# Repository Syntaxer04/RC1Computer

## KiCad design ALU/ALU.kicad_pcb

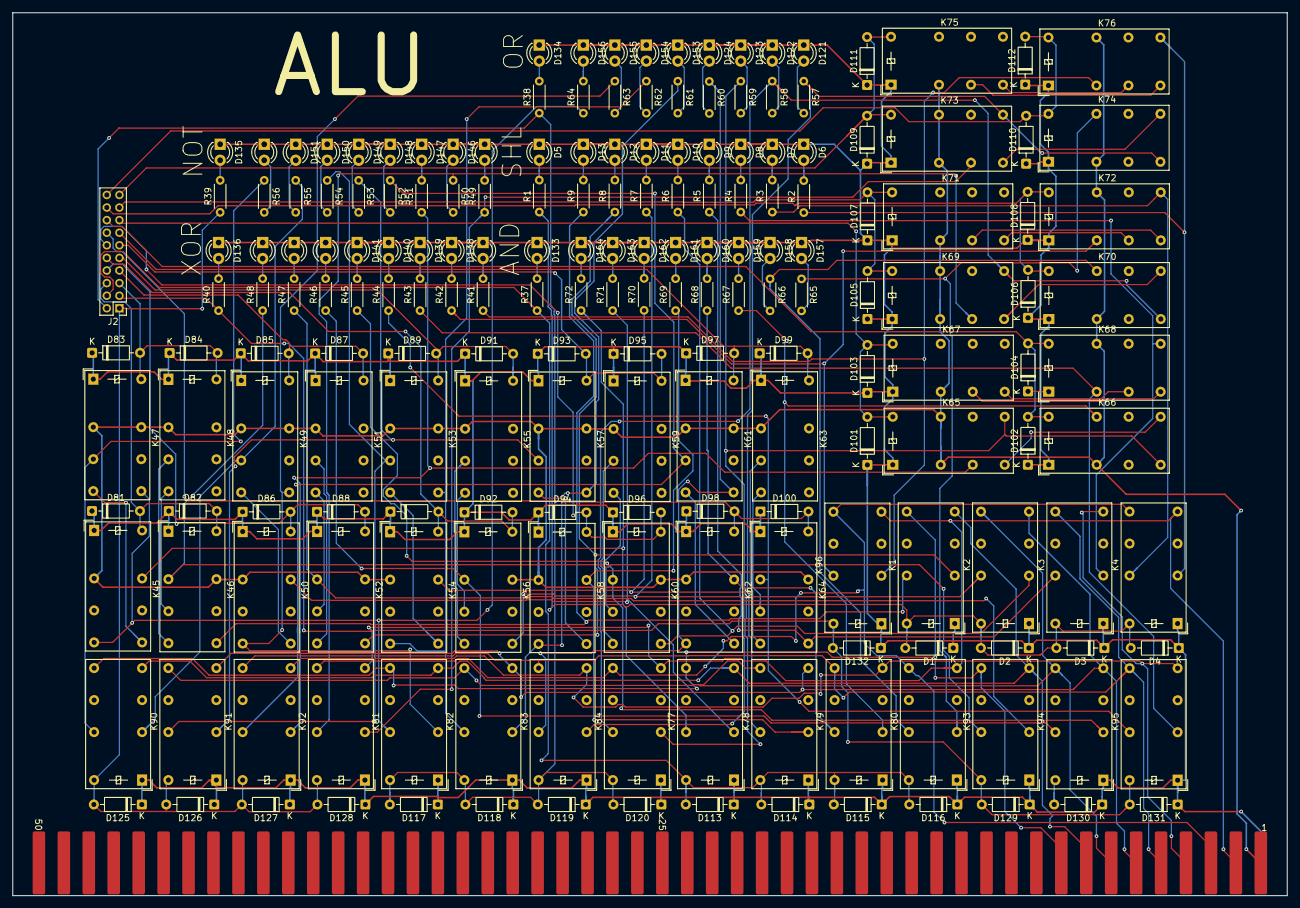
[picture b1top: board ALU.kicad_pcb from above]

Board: 2 copper layers, 202.4 x 140.2 mm, 196 parts (0 on the bottom side), 142 nets.

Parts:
D1, D2, D3, D4, D81, D82, D83, D84, D85, D86, D87, D88, D89, D90, D91, D92, D93, D94, D95, D96, D97, D98, D99, D100, D101, D102, D103, D104, D105, D106, D107, D108, D109, D110, D111, D112, D113, D114, D115, D116, D117, D118, D119, D120, D125, D126, D127, D128, D129, D130, D131, D132: 1N914; D_DO-35_SOD27_P7.62mm_Horizontal
D5, D6, D7, D8, D9, D10, D11, D12, D13, D121, D122, D123, D124, D133, D134, D135, D136, D137, D138, D139, D140, D141, D142, D143, D144, D145, D146, D147, D148, D149, D150, D151, D152, D153, D154, D155, D156, D157, D158, D159, D160, D161, D162, D163, D164: LED; LED_D3.0mm
J2: Conn_02x10_Odd_Even; PinHeader_2x10_P2.00mm_Vertical
K1, K2, K3, K4, K45, K46, K47, K48, K49, K50, K51, K52, K53, K54, K55, K56, K57, K58, K59, K60, K61, K62, K63, K64, K65, K66, K67, K68, K69, K70, K71, K72, K73, K74, K75, K76, K77, K78, K79, K80, K81, K82, K83, K84, K89, K90, K91, K92, K93, K94, K95, K96: HK19F-DCxxV-SHC; Relay_DPDT_Finder_30.22
R1, R2, R3, R4, R5, R6, R7, R8, R9, R37, R38, R39, R40, R41, R42, R43, R44, R45, R46, R47, R48, R49, R50, R51, R52, R53, R54, R55, R56, R57, R58, R59, R60, R61, R62, R63, R64, R65, R66, R67, R68, R69, R70, R71, R72: R; R_Axial_DIN0204_L3.6mm_D1.6mm_P5.08mm_Horizontal
U1: Conn_RC_Male_100

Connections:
unnamed: D1.2 (A), D2.2 (A), D3.2 (A), D4.2 (A), K1.A2, K2.A2, K3.A2, K4.A2, R1.1
unnamed: D1.1 (K), D2.1 (K), D3.1 (K), D4.1 (K), D5.1 (K), D6.1 (K), D7.1 (K), D8.1 (K), D9.1 (K), D10.1 (K), D11.1 (K), D12.1 (K), D13.1 (K), D81.1 (K), D82.1 (K), D83.1 (K), D84.1 (K), D85.1 (K), D86.1 (K), D87.1 (K), D88.1 (K), D89.1 (K), D90.1 (K), D91.1 (K), D92.1 (K), D93.1 (K), D94.1 (K), D95.1 (K), D96.1 (K), D97.1 (K), D98.1 (K), D99.1 (K), D100.1 (K), D101.1 (K), D102.1 (K), D103.1 (K), D105.1 (K), D106.1 (K), D107.1 (K), D108.1 (K), D109.1 (K), D110.1 (K), D111.1 (K), D112.1 (K), D113.1 (K), D114.1 (K), D115.1 (K), D116.1 (K), D117.1 (K), D118.1 (K), D119.1 (K), D120.1 (K), D121.1 (K), D122.1 (K), D123.1 (K), D124.1 (K), D125.1 (K), D126.1 (K), D127.1 (K), D128.1 (K), D129.1 (K), D130.1 (K), D131.1 (K), D132.1 (K), D133.1 (K), D134.1 (K), D135.1 (K), D136.1 (K), D137.1 (K), D138.1 (K), D139.1 (K), D140.1 (K), D141.1 (K), D142.1 (K), D143.1 (K), D144.1 (K), D145.1 (K), D146.1 (K), D147.1 (K), D148.1 (K), D149.1 (K), D150.1 (K), D151.1 (K), D152.1 (K), D153.1 (K), D154.1 (K), D155.1 (K), D156.1 (K), D157.1 (K), D158.1 (K), D159.1 (K), D160.1 (K), D161.1 (K), D162.1 (K), D163.1 (K), D164.1 (K), K1.A1, K2.A1, K3.A1, K4.A1, K45.A1, K46.A1, K47.A1, K48.A1, K49.A1, K50.A1, K51.A1, K52.A1, K53.A1, K54.A1, K55.A1, K56.A1, K57.A1, K58.A1, K59.A1, K60.A1, K61.A1, K62.A1, K63.A1, K64.A1, K65.A1, K66.A1, K67.A1, K69.A1, K70.A1, K71.A1, K72.A1, K73.A1, K74.A1, K75.A1, K76.A1, K77.A1, K78.A1, K79.A1, K80.A1, K81.A1, K82.A1, K83.A1, K84.A1, K89.A1, K90.A1, K91.A1, K92.A1, K93.A1, K94.A1, K95.A1, K96.A1, U1.51 (GND)
unnamed: D5.2 (A), R1.2
unnamed: D6.2 (A), R2.2
unnamed: D7.2 (A), R3.2
unnamed: D8.2 (A), R4.2
unnamed: D9.2 (A), R5.2
unnamed: D10.2 (A), R6.2
unnamed: D11.2 (A), R7.2
unnamed: D12.2 (A), R8.2
unnamed: D13.2 (A), R9.2
unnamed: D81.2 (A), D82.2 (A), J2.6, K45.A2, K46.A2
unnamed: D83.2 (A), D84.2 (A), J2.5, K47.A2, K48.A2
unnamed: D85.2 (A), D87.2 (A), J2.7, K49.A2, K51.A2
unnamed: D86.2 (A), D88.2 (A), J2.8, K50.A2, K52.A2
unnamed: D89.2 (A), D91.2 (A), J2.9, K53.A2, K55.A2
unnamed: D90.2 (A), D92.2 (A), J2.10, K54.A2, K56.A2
unnamed: D93.2 (A), D95.2 (A), J2.11, K57.A2, K59.A2
unnamed: D94.2 (A), D96.2 (A), J2.12, K58.A2, K60.A2
unnamed: D97.2 (A), D99.2 (A), J2.13, K61.A2, K63.A2
unnamed: D98.2 (A), D100.2 (A), J2.14, K62.A2, K64.A2
unnamed: D101.2 (A), D103.2 (A), J2.15, K65.A2, K67.A2
unnamed: D102.2 (A), D104.2 (A), J2.16, K66.A2, K68.A2
unnamed: D104.1 (K), K68.A1
unnamed: D105.2 (A), D107.2 (A), J2.17, K69.A2, K71.A2
unnamed: D106.2 (A), D108.2 (A), J2.18, K70.A2, K72.A2
unnamed: D109.2 (A), D111.2 (A), J2.19, K73.A2, K75.A2
unnamed: D110.2 (A), D112.2 (A), J2.20, K74.A2, K76.A2
unnamed: D113.2 (A), D114.2 (A), D115.2 (A), D116.2 (A), J2.4, K77.A2, K78.A2, K79.A2, K80.A2, R37.1
unnamed: D117.2 (A), D118.2 (A), D119.2 (A), D120.2 (A), J2.2, K81.A2, K82.A2, K83.A2, K84.A2, R38.1
unnamed: D121.2 (A), R57.2
unnamed: D122.2 (A), R58.2
unnamed: D123.2 (A), R59.2
unnamed: D124.2 (A), R60.2
unnamed: D125.2 (A), D126.2 (A), D127.2 (A), D128.2 (A), J2.1, K89.A2, K90.A2, K91.A2, K92.A2, R39.1
unnamed: D129.2 (A), D131.2 (A), D132.2 (A), J2.3, K93.A2, K95.A2, K96.A2, R40.1
unnamed: D130.2 (A), K94.A2
unnamed: D133.2 (A), R37.2
unnamed: D134.2 (A), R38.2
unnamed: D135.2 (A), R39.2
unnamed: D136.2 (A), R40.2
unnamed: D137.2 (A), R41.2
unnamed: D138.2 (A), R42.2
unnamed: D139.2 (A), R43.2
unnamed: D140.2 (A), R44.2
unnamed: D141.2 (A), R45.2
unnamed: D142.2 (A), R46.2
unnamed: D143.2 (A), R47.2
unnamed: D144.2 (A), R48.2
unnamed: D145.2 (A), R49.2
unnamed: D146.2 (A), R50.2
unnamed: D147.2 (A), R51.2
unnamed: D148.2 (A), R52.2
unnamed: D149.2 (A), R53.2
unnamed: D150.2 (A), R54.2
unnamed: D151.2 (A), R55.2
unnamed: D152.2 (A), R56.2
unnamed: D153.2 (A), R61.2
unnamed: D154.2 (A), R62.2
unnamed: D155.2 (A), R63.2
unnamed: D156.2 (A), R64.2
unnamed: D157.2 (A), R65.2
unnamed: D158.2 (A), R66.2
unnamed: D159.2 (A), R67.2
unnamed: D160.2 (A), R68.2
unnamed: D161.2 (A), R69.2
unnamed: D162.2 (A), R70.2
unnamed: D163.2 (A), R71.2
unnamed: D164.2 (A), R72.2
unnamed: K1.11, K52.24, R8.1
unnamed: K1.21, K46.24, R9.1
unnamed: K2.11, K60.24, R6.1
unnamed: K2.21, K56.24, R7.1
unnamed: K3.11, K68.24, R4.1
unnamed: K3.21, K64.24, R5.1
unnamed: K4.11, K76.24, R2.1
unnamed: K4.21, K72.24, R3.1
unnamed: K45.14, K47.24, K81.21, R64.1
unnamed: K45.21, K77.21, R72.1
unnamed: K45.24, K47.14
unnamed: K46.11, K93.21, R48.1
unnamed: K46.12, K48.14
unnamed: K46.14, K48.12
unnamed: K47.12, K89.21, R56.1
unnamed: K49.12, K89.11, R55.1
unnamed: K49.14, K50.24
unnamed: K49.24, K50.14, K81.11, R63.1
unnamed: K50.21, K77.11, R71.1
unnamed: K51.12, K52.14
unnamed: K51.14, K52.12
unnamed: K52.11, K93.11, R47.1
unnamed: K53.12, K90.21, R54.1
unnamed: K53.14, K54.24
unnamed: K53.24, K54.14, K82.21, R62.1
unnamed: K54.21, K78.21, R70.1
unnamed: K55.12, K56.14
unnamed: K55.14, K56.12
unnamed: K56.11, K94.21, R46.1
unnamed: K57.12, K90.11, R53.1
unnamed: K57.14, K58.24
unnamed: K57.24, K58.14, K82.11, R61.1
unnamed: K58.21, K78.11, R69.1
unnamed: K59.12, K60.14
unnamed: K59.14, K60.12
unnamed: K60.11, K94.11, R45.1
unnamed: K61.12, K91.21, R52.1
unnamed: K61.14, K62.24
unnamed: K61.24, K62.14, K83.21, R60.1
unnamed: K62.21, K79.21, R68.1
unnamed: K63.12, K64.14
unnamed: K63.14, K64.12
unnamed: K64.11, K95.21, R44.1
unnamed: K65.12, K91.11, R51.1
unnamed: K65.14, K66.24
unnamed: K65.24, K66.14, K83.11, R59.1
unnamed: K66.21, K79.11, R67.1
unnamed: K67.12, K68.14
unnamed: K67.14, K68.12
unnamed: K68.11, K95.11, R43.1
unnamed: K69.12, K92.21, R50.1
unnamed: K69.14, K70.24
unnamed: K69.24, K70.14, K84.21, R58.1
unnamed: K70.21, K80.21, R66.1
unnamed: K71.12, K72.14
unnamed: K71.14, K72.12
unnamed: K72.11, K96.21, R42.1
unnamed: K73.12, K92.11, R49.1
unnamed: K73.14, K74.24
unnamed: K73.24, K74.14, K84.11, R57.1
unnamed: K74.21, K80.11, R65.1
unnamed: K75.12, K76.14
unnamed: K75.14, K76.12
unnamed: K76.11, K96.11, R41.1
unnamed: K45.11, K46.21, K47.11, K47.21, K48.11, K49.11, K49.21, K50.11, K51.11, K52.21, K53.11, K53.21, K54.11, K55.11, K56.21, K57.11, K57.21, K58.11, K59.11, K60.21, K61.11, K61.21, K62.11, K63.11, K64.21, K65.11, K65.21, K66.11, K67.11, K68.21, K69.11, K69.21, K70.11, K71.11, K72.21, K73.11, K73.21, K74.11, K75.11, K76.21, U1.1 (5_Volt)
unnamed: K4.14, K80.14, K84.14, K92.14, K96.14, U1.2 (D0)
unnamed: K4.24, K80.24, K84.24, K92.24, K96.24, U1.3 (D1)
unnamed: K3.14, K79.14, K83.14, K91.14, K95.14, U1.4 (D2)
unnamed: K3.24, K79.24, K83.24, K91.24, K95.24, U1.5 (D3)
unnamed: K2.14, K78.14, K82.14, K90.14, K94.14, U1.6 (D4)
unnamed: K2.24, K78.24, K82.24, K90.24, K94.24, U1.7 (D5)
unnamed: K1.14, K77.14, K81.14, K89.14, K93.14, U1.8 (D6)
unnamed: K1.24, K77.24, K81.24, K89.24, K93.24, U1.9 (D7)

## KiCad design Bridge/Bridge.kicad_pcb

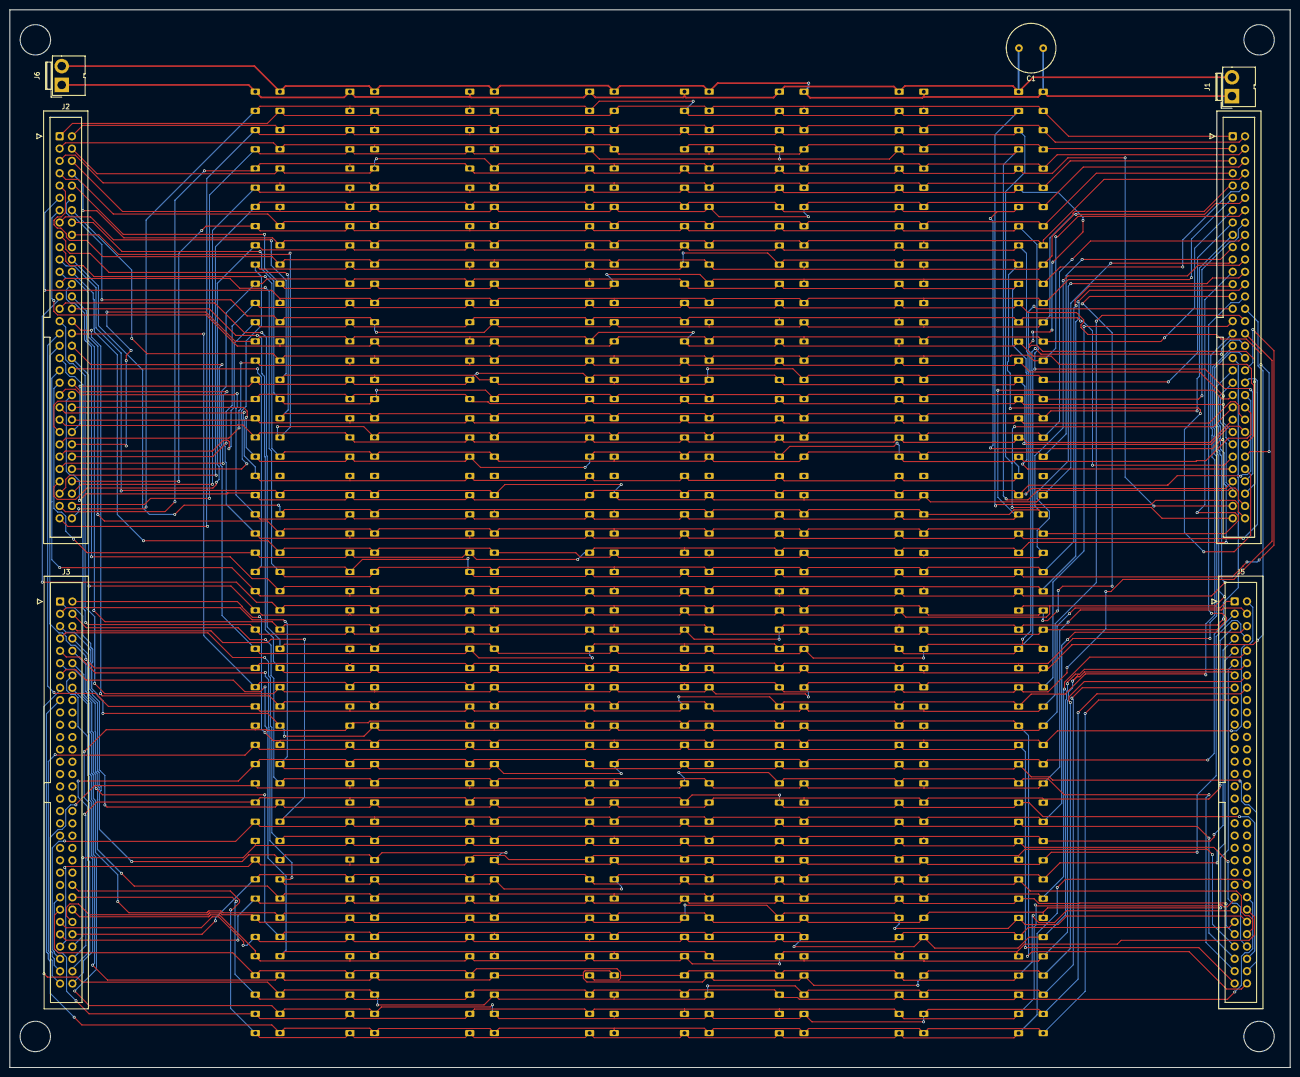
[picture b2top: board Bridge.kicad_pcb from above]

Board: 2 copper layers, 263.9 x 218.0 mm, 15 parts (0 on the bottom side), 99 nets.

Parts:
C1: C; C_Radial_D10.0mm_H12.5mm_P5.00mm
J1, J6: Conn_01x02_Socket; JWT_A3963_1x02_P3.96mm_Vertical
J2, J3, J4, J5: Conn_02x32_Counter_Clockwise; IDC-Header_2x32_P2.54mm_Vertical
U1, U2, U3, U4, U5, U6, U7, U8: Conn_RC_Female_100

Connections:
A0: J3.5, J5.5, U1.38 (A0), U2.38 (A0), U3.38 (A0), U4.38 (A0), U5.38 (A0), U6.38 (A0), U7.38 (A0), U8.38 (A0)
A1: J3.6, J5.6, U1.39 (A1), U2.39 (A1), U3.39 (A1), U4.39 (A1), U5.39 (A1), U6.39 (A1), U7.39 (A1), U8.39 (A1)
A2: J3.7, J5.7, U1.40 (A2), U2.40 (A2), U3.40 (A2), U4.40 (A2), U5.40 (A2), U6.40 (A2), U7.40 (A2), U8.40 (A2)
A3: J3.8, J5.8, U1.41 (A3), U2.41 (A3), U3.41 (A3), U4.41 (A3), U5.41 (A3), U6.41 (A3), U7.41 (A3), U8.41 (A3)
A4: J3.9, J5.9, U1.42 (A4), U2.42 (A4), U3.42 (A4), U4.42 (A4), U5.42 (A4), U6.42 (A4), U7.42 (A4), U8.42 (A4)
A5: J3.10, J5.10, U1.43 (A5), U2.43 (A5), U3.43 (A5), U4.43 (A5), U5.43 (A5), U6.43 (A5), U7.43 (A5), U8.43 (A5)
A6: J3.11, J5.11, U1.44 (A6), U2.44 (A6), U3.44 (A6), U4.44 (A6), U5.44 (A6), U6.44 (A6), U7.44 (A6), U8.44 (A6)
A7: J3.12, J5.12, U1.45 (A7), U2.45 (A7), U3.45 (A7), U4.45 (A7), U5.45 (A7), U6.45 (A7), U7.45 (A7), U8.45 (A7)
A8: J3.13, J5.13, U1.46 (A8), U2.46 (A8), U3.46 (A8), U4.46 (A8), U5.46 (A8), U6.46 (A8), U7.46 (A8), U8.46 (A8)
A9: J3.14, J5.14, U1.47 (A9), U2.47 (A9), U3.47 (A9), U4.47 (A9), U5.47 (A9), U6.47 (A9), U7.47 (A9), U8.47 (A9)
A10: J3.15, J5.15, U1.48 (A10), U2.48 (A10), U3.48 (A10), U4.48 (A10), U5.48 (A10), U6.48 (A10), U7.48 (A10), U8.48 (A10)
A11: J3.16, J5.16, U1.49 (A11), U2.49 (A11), U3.49 (A11), U4.49 (A11), U5.49 (A11), U6.49 (A11), U7.49 (A11), U8.49 (A11)
A12: J3.17, J5.17, U1.50 (A12), U2.50 (A12), U3.50 (A12), U4.50 (A12), U5.50 (A12), U6.50 (A12), U7.50 (A12), U8.50 (A12)
A13: J2.64, J4.64, U1.52 (A13), U2.52 (A13), U3.52 (A13), U4.52 (A13), U5.52 (A13), U6.52 (A13), U7.52 (A13), U8.52 (A13)
A14: J2.63, J4.63, U1.53 (A14), U2.53 (A14), U3.53 (A14), U4.53 (A14), U5.53 (A14), U6.53 (A14), U7.53 (A14), U8.53 (A14)
A15: J2.62, J4.62, U1.54 (A15), U2.54 (A15), U3.54 (A15), U4.54 (A15), U5.54 (A15), U6.54 (A15), U7.54 (A15), U8.54 (A15)
ALD: J2.18, J4.18, U1.19 (ALD), U2.19 (ALD), U3.19 (ALD), U4.19 (ALD), U5.19 (ALD), U6.19 (ALD), U7.19 (ALD), U8.19 (ALD)
ASL: J2.22, J4.22, U1.23 (ASL), U2.23 (ASL), U3.23 (ASL), U4.23 (ASL), U5.23 (ASL), U6.23 (ASL), U7.23 (ASL), U8.23 (ASL)
BLD: J2.42, J4.42, U1.74 (BLD), U2.74 (BLD), U3.74 (BLD), U4.74 (BLD), U5.74 (BLD), U6.74 (BLD), U7.74 (BLD), U8.74 (BLD)
BSL: J2.44, J4.44, U1.72 (BSL), U2.72 (BSL), U3.72 (BSL), U4.72 (BSL), U5.72 (BSL), U6.72 (BSL), U7.72 (BSL), U8.72 (BSL)
CCRegLD: J2.35, J4.35, U1.81 (CCRegLD), U2.81 (CCRegLD), U3.81 (CCRegLD), U4.81 (CCRegLD), U5.81 (CCRegLD), U6.81 (CCRegLD), U7.81 (CCRegLD), U8.81 (CCRegLD)
CCRegSL: J2.34, J4.34, U1.82 (CCRegSL), U2.82 (CCRegSL), U3.82 (CCRegSL), U4.82 (CCRegSL), U5.82 (CCRegSL), U6.82 (CCRegSL), U7.82 (CCRegSL), U8.82 (CCRegSL)
CLD: J2.41, J4.41, U1.75 (CLD), U2.75 (CLD), U3.75 (CLD), U4.75 (CLD), U5.75 (CLD), U6.75 (CLD), U7.75 (CLD), U8.75 (CLD)
CSL: J2.43, J4.43, U1.73 (CSL), U2.73 (CSL), U3.73 (CSL), U4.73 (CSL), U5.73 (CSL), U6.73 (CSL), U7.73 (CSL), U8.73 (CSL)
Carry: J3.2, J5.2, U1.35 (Carry), U2.35 (Carry), U3.35 (Carry), U4.35 (Carry), U5.35 (Carry), U6.35 (Carry), U7.35 (Carry), U8.35 (Carry)
D0: J2.1, J4.1, U1.2 (D0), U2.2 (D0), U3.2 (D0), U4.2 (D0), U5.2 (D0), U6.2 (D0), U7.2 (D0), U8.2 (D0)
D1: J2.2, J4.2, U1.3 (D1), U2.3 (D1), U3.3 (D1), U4.3 (D1), U5.3 (D1), U6.3 (D1), U7.3 (D1), U8.3 (D1)
D2: J2.3, J4.3, U1.4 (D2), U2.4 (D2), U3.4 (D2), U4.4 (D2), U5.4 (D2), U6.4 (D2), U7.4 (D2), U8.4 (D2)
D3: J2.4, J4.4, U1.5 (D3), U2.5 (D3), U3.5 (D3), U4.5 (D3), U5.5 (D3), U6.5 (D3), U7.5 (D3), U8.5 (D3)
D4: J2.5, J4.5, U1.6 (D4), U2.6 (D4), U3.6 (D4), U4.6 (D4), U5.6 (D4), U6.6 (D4), U7.6 (D4), U8.6 (D4)
D5: J2.6, J4.6, U1.7 (D5), U2.7 (D5), U3.7 (D5), U4.7 (D5), U5.7 (D5), U6.7 (D5), U7.7 (D5), U8.7 (D5)
D6: J2.7, J4.7, U1.8 (D6), U2.8 (D6), U3.8 (D6), U4.8 (D6), U5.8 (D6), U6.8 (D6), U7.8 (D6), U8.8 (D6)
D7: J2.8, J4.8, U1.9 (D7), U2.9 (D7), U3.9 (D7), U4.9 (D7), U5.9 (D7), U6.9 (D7), U7.9 (D7), U8.9 (D7)
DLD: J2.19, J4.19, U1.20 (DLD), U2.20 (DLD), U3.20 (DLD), U4.20 (DLD), U5.20 (DLD), U6.20 (DLD), U7.20 (DLD), U8.20 (DLD)
DSL: J2.23, J4.23, U1.24 (DSL), U2.24 (DSL), U3.24 (DSL), U4.24 (DSL), U5.24 (DSL), U6.24 (DSL), U7.24 (DSL), U8.24 (DSL)
F1: J2.31, J4.31, U1.32 (F1), U2.32 (F1), U3.32 (F1), U4.32 (F1), U5.32 (F1), U6.32 (F1), U7.32 (F1), U8.32 (F1)
F2: J2.32, J4.32, U1.33 (F2), U2.33 (F2), U3.33 (F2), U4.33 (F2), U5.33 (F2), U6.33 (F2), U7.33 (F2), U8.33 (F2)
F3: J3.1, J5.1, U1.34 (F3), U2.34 (F3), U3.34 (F3), U4.34 (F3), U5.34 (F3), U6.34 (F3), U7.34 (F3), U8.34 (F3)
FREEZE: J2.39, J4.39, U1.77 (FREEZE), U2.77 (FREEZE), U3.77 (FREEZE), U4.77 (FREEZE), U5.77 (FREEZE), U6.77 (FREEZE), U7.77 (FREEZE), U8.77 (FREEZE)
HALT: J3.63, J5.63, U1.85 (HALT), U2.85 (HALT), U3.85 (HALT), U4.85 (HALT), U5.85 (HALT), U6.85 (HALT), U7.85 (HALT), U8.85 (HALT)
I0: J2.47, J4.47, U1.69 (I0), U2.69 (I0), U3.69 (I0), U4.69 (I0), U5.69 (I0), U6.69 (I0), U7.69 (I0), U8.69 (I0)
I1: J2.48, J4.48, U1.68 (I1), U2.68 (I1), U3.68 (I1), U4.68 (I1), U5.68 (I1), U6.68 (I1), U7.68 (I1), U8.68 (I1)
I2: J2.49, J4.49, U1.67 (I2), U2.67 (I2), U3.67 (I2), U4.67 (I2), U5.67 (I2), U6.67 (I2), U7.67 (I2), U8.67 (I2)
I3: J2.50, J4.50, U1.66 (I3), U2.66 (I3), U3.66 (I3), U4.66 (I3), U5.66 (I3), U6.66 (I3), U7.66 (I3), U8.66 (I3)
I4: J2.51, J4.51, U1.65 (I4), U2.65 (I4), U3.65 (I4), U4.65 (I4), U5.65 (I4), U6.65 (I4), U7.65 (I4), U8.65 (I4)
I5: J2.52, J4.52, U1.64 (I5), U2.64 (I5), U3.64 (I5), U4.64 (I5), U5.64 (I5), U6.64 (I5), U7.64 (I5), U8.64 (I5)
I6: J2.53, J4.53, U1.63 (I6), U2.63 (I6), U3.63 (I6), U4.63 (I6), U5.63 (I6), U6.63 (I6), U7.63 (I6), U8.63 (I6)
I7: J2.54, J4.54, U1.62 (I7), U2.62 (I7), U3.62 (I7), U4.62 (I7), U5.62 (I7), U6.62 (I7), U7.62 (I7), U8.62 (I7)
IALU: J2.59, J4.59, U1.57 (IALU), U2.57 (IALU), U3.57 (IALU), U4.57 (IALU), U5.57 (IALU), U6.57 (IALU), U7.57 (IALU), U8.57 (IALU)
IGOTO: J2.60, J4.60, U1.56 (IGOTO), U2.56 (IGOTO), U3.56 (IGOTO), U4.56 (IGOTO), U5.56 (IGOTO), U6.56 (IGOTO), U7.56 (IGOTO), U8.56 (IGOTO)
IINC: J2.58, J4.58, U1.58 (IINC), U2.58 (IINC), U3.58 (IINC), U4.58 (IINC), U5.58 (IINC), U6.58 (IINC), U7.58 (IINC), U8.58 (IINC)
ILOD: J2.57, J4.57, U1.59 (ILOD), U2.59 (ILOD), U3.59 (ILOD), U4.59 (ILOD), U5.59 (ILOD), U6.59 (ILOD), U7.59 (ILOD), U8.59 (ILOD)
IM16: J2.55, J4.55, U1.61 (IM16), U2.61 (IM16), U3.61 (IM16), U4.61 (IM16), U5.61 (IM16), U6.61 (IM16), U7.61 (IM16), U8.61 (IM16)
ISET: J2.61, J4.61, U1.55 (ISET), U2.55 (ISET), U3.55 (ISET), U4.55 (ISET), U5.55 (ISET), U6.55 (ISET), U7.55 (ISET), U8.55 (ISET)
ISTR: J2.56, J4.56, U1.60 (ISTR), U2.60 (ISTR), U3.60 (ISTR), U4.60 (ISTR), U5.60 (ISTR), U6.60 (ISTR), U7.60 (ISTR), U8.60 (ISTR)
IncLD: J2.40, J4.40, U1.76 (INCLD), U2.76 (INCLD), U3.76 (INCLD), U4.76 (INCLD), U5.76 (INCLD), U6.76 (INCLD), U7.76 (INCLD), U8.76 (INCLD)
IncSL: J2.26, J4.26, U1.27 (IncSL), U2.27 (IncSL), U3.27 (IncSL), U4.27 (IncSL), U5.27 (IncSL), U6.27 (IncSL), U7.27 (IncSL), U8.27 (IncSL)
InstLD: J2.36, J4.36, U1.80 (INSTLD), U2.80 (INSTLD), U3.80 (INSTLD), U4.80 (INSTLD), U5.80 (INSTLD), U6.80 (INSTLD), U7.80 (INSTLD), U8.80 (INSTLD)
InstSL: J2.24, J4.24, U1.25 (InstSL), U2.25 (InstSL), U3.25 (InstSL), U4.25 (InstSL), U5.25 (InstSL), U6.25 (InstSL), U7.25 (InstSL), U8.25 (InstSL)
J1LD: J2.15, J4.15, U1.16 (J1LD), U2.16 (J1LD), U3.16 (J1LD), U4.16 (J1LD), U5.16 (J1LD), U6.16 (J1LD), U7.16 (J1LD), U8.16 (J1LD)
J2LD: J2.16, J4.16, U1.17 (J2LD), U2.17 (J2LD), U3.17 (J2LD), U4.17 (J2LD), U5.17 (J2LD), U6.17 (J2LD), U7.17 (J2LD), U8.17 (J2LD)
JSL: J2.17, J4.17, U1.18 (JSL), U2.18 (JSL), U3.18 (JSL), U4.18 (JSL), U5.18 (JSL), U6.18 (JSL), U7.18 (JSL), U8.18 (JSL)
MEMCS: J3.64, J5.64, U1.84 (MEMSL), U2.84 (MEMSL), U3.84 (MEMSL), U4.84 (MEMSL), U5.84 (MEMSL), U6.84 (MEMSL), U7.84 (MEMSL), U8.84 (MEMSL)
MEMWRITE: J2.33, J4.33, U1.83 (MEMWRITE), U2.83 (MEMWRITE), U3.83 (MEMWRITE), U4.83 (MEMWRITE), U5.83 (MEMWRITE), U6.83 (MEMWRITE), U7.83 (MEMWRITE), U8.83 (MEMWRITE)
MHiLD: J2.12, J4.12, U1.13 (MHiLD), U2.13 (MHiLD), U3.13 (MHiLD), U4.13 (MHiLD), U5.13 (MHiLD), U6.13 (MHiLD), U7.13 (MHiLD), U8.13 (MHiLD)
MHiLoLD: J2.14, J4.14, U1.15 (MHiLoLD), U2.15 (MHiLoLD), U3.15 (MHiLoLD), U4.15 (MHiLoLD), U5.15 (MHiLoLD), U6.15 (MHiLoLD), U7.15 (MHiLoLD), U8.15 (MHiLoLD)
MHiSL: J2.46, J4.46, U1.70 (MHiSL), U2.70 (MHiSL), U3.70 (MHiSL), U4.70 (MHiSL), U5.70 (MHiSL), U6.70 (MHiSL), U7.70 (MHiSL), U8.70 (MHiSL)
MLoLD: J2.13, J4.13, U1.14 (MLoLD), U2.14 (MLoLD), U3.14 (MLoLD), U4.14 (MLoLD), U5.14 (MLoLD), U6.14 (MLoLD), U7.14 (MLoLD), U8.14 (MLoLD)
MLoSL: J2.45, J4.45, U1.71 (MLoSL), U2.71 (MLoSL), U3.71 (MLoSL), U4.71 (MLoSL), U5.71 (MLoSL), U6.71 (MLoSL), U7.71 (MLoSL), U8.71 (MLoSL)
MemREAD: J2.37, J4.37, U1.79 (MEMREAD), U2.79 (MEMREAD), U3.79 (MEMREAD), U4.79 (MEMREAD), U5.79 (MEMREAD), U6.79 (MEMREAD), U7.79 (MEMREAD), U8.79 (MEMREAD)
MemSL: J2.21, J4.21, U1.22 (MemSL), U2.22 (MemSL), U3.22 (MemSL), U4.22 (MemSL), U5.22 (MemSL), U6.22 (MemSL), U7.22 (MemSL), U8.22 (MemSL)
N0: J3.62, J5.62, U1.86 (NC), U2.86 (NC), U3.86 (NC), U4.86 (NC), U5.86 (NC), U6.86 (NC), U7.86 (NC), U8.86 (NC)
N1: J3.61, J5.61, U1.87 (NC), U2.87 (NC), U3.87 (NC), U4.87 (NC), U5.87 (NC), U6.87 (NC), U7.87 (NC), U8.87 (NC)
N2: J3.60, J5.60, U1.88 (NC), U2.88 (NC), U3.88 (NC), U4.88 (NC), U5.88 (NC), U6.88 (NC), U7.88 (NC), U8.88 (NC)
N3: J3.59, J5.59, U1.89 (NC), U2.89 (NC), U3.89 (NC), U4.89 (NC), U5.89 (NC), U6.89 (NC), U7.89 (NC), U8.89 (NC)
N4: J3.58, J5.58, U1.90 (NC), U2.90 (NC), U3.90 (NC), U4.90 (NC), U5.90 (NC), U6.90 (NC), U7.90 (NC), U8.90 (NC)
N5: J3.57, J5.57, U1.91 (NC), U2.91 (NC), U3.91 (NC), U4.91 (NC), U5.91 (NC), U6.91 (NC), U7.91 (NC), U8.91 (NC)
N6: J3.56, J5.56, U1.92 (NC), U2.92 (NC), U3.92 (NC), U4.92 (NC), U5.92 (NC), U6.92 (NC), U7.92 (NC), U8.92 (NC)
N7: J3.55, J5.55, U1.93 (NC), U2.93 (NC), U3.93 (NC), U4.93 (NC), U5.93 (NC), U6.93 (NC), U7.93 (NC), U8.93 (NC)
N8: J3.54, J5.54, U1.94 (NC), U2.94 (NC), U3.94 (NC), U4.94 (NC), U5.94 (NC), U6.94 (NC), U7.94 (NC), U8.94 (NC)
N9: J3.53, J5.53, U1.95 (NC), U2.95 (NC), U3.95 (NC), U4.95 (NC), U5.95 (NC), U6.95 (NC), U7.95 (NC), U8.95 (NC)
N10: J3.52, J5.52, U1.96 (NC), U2.96 (NC), U3.96 (NC), U4.96 (NC), U5.96 (NC), U6.96 (NC), U7.96 (NC), U8.96 (NC)
N11: J3.51, J5.51, U1.97 (NC), U2.97 (NC), U3.97 (NC), U4.97 (NC), U5.97 (NC), U6.97 (NC), U7.97 (NC), U8.97 (NC)
N12: J3.50, J5.50, U1.98 (NC), U2.98 (NC), U3.98 (NC), U4.98 (NC), U5.98 (NC), U6.98 (NC), U7.98 (NC), U8.98 (NC)
N13: J3.49, J5.49, U1.99 (NC), U2.99 (NC), U3.99 (NC), U4.99 (NC), U5.99 (NC), U6.99 (NC), U7.99 (NC), U8.99 (NC)
N14: J3.48, J5.48, U1.100 (NC), U2.100 (NC), U3.100 (NC), U4.100 (NC), U5.100 (NC), U6.100 (NC), U7.100 (NC), U8.100 (NC)
unnamed: C1.1, J1.1, J6.2, U1.1 (5_Volt), U2.1 (5_Volt), U3.1 (5_Volt), U4.1 (5_Volt), U5.1 (5_Volt), U6.1 (5_Volt), U7.1 (5_Volt), U8.1 (5_Volt)
unnamed: C1.2, J1.2, J6.1, U1.51 (GND), U2.51 (GND), U3.51 (GND), U4.51 (GND), U5.51 (GND), U6.51 (GND), U7.51 (GND), U8.51 (GND)
PCLD: J2.30, J4.30, U1.31 (PCLD), U2.31 (PCLD), U3.31 (PCLD), U4.31 (PCLD), U5.31 (PCLD), U6.31 (PCLD), U7.31 (PCLD), U8.31 (PCLD)
PCSL: J2.25, J4.25, U1.26 (PCSL), U2.26 (PCSL), U3.26 (PCSL), U4.26 (PCSL), U5.26 (PCSL), U6.26 (PCSL), U7.26 (PCSL), U8.26 (PCSL)
SIGN: J3.4, J5.4, U1.37 (SIGN), U2.37 (SIGN), U3.37 (SIGN), U4.37 (SIGN), U5.37 (SIGN), U6.37 (SIGN), U7.37 (SIGN), U8.37 (SIGN)
STEP: J2.38, J4.38, U1.78 (STEP), U2.78 (STEP), U3.78 (STEP), U4.78 (STEP), U5.78 (STEP), U6.78 (STEP), U7.78 (STEP), U8.78 (STEP)
XLD: J2.9, J4.9, U1.10 (XLD), U2.10 (XLD), U3.10 (XLD), U4.10 (XLD), U5.10 (XLD), U6.10 (XLD), U7.10 (XLD), U8.10 (XLD)
XSL: J2.27, J4.27, U1.28 (XSL), U2.28 (XSL), U3.28 (XSL), U4.28 (XSL), U5.28 (XSL), U6.28 (XSL), U7.28 (XSL), U8.28 (XSL)
XYLD: J2.11, J4.11, U1.12 (XYLD), U2.12 (XYLD), U3.12 (XYLD), U4.12 (XYLD), U5.12 (XYLD), U6.12 (XYLD), U7.12 (XYLD), U8.12 (XYLD)
XYSL: J2.29, J4.29, U1.30 (XYSL), U2.30 (XYSL), U3.30 (XYSL), U4.30 (XYSL), U5.30 (XYSL), U6.30 (XYSL), U7.30 (XYSL), U8.30 (XYSL)
YLD: J2.10, J4.10, U1.11 (YLD), U2.11 (YLD), U3.11 (YLD), U4.11 (YLD), U5.11 (YLD), U6.11 (YLD), U7.11 (YLD), U8.11 (YLD)
YSL: J2.28, J4.28, U1.29 (YSL), U2.29 (YSL), U3.29 (YSL), U4.29 (YSL), U5.29 (YSL), U6.29 (YSL), U7.29 (YSL), U8.29 (YSL)
Zero: J3.3, J5.3, U1.36 (Zero), U2.36 (Zero), U3.36 (Zero), U4.36 (Zero), U5.36 (Zero), U6.36 (Zero), U7.36 (Zero), U8.36 (Zero)

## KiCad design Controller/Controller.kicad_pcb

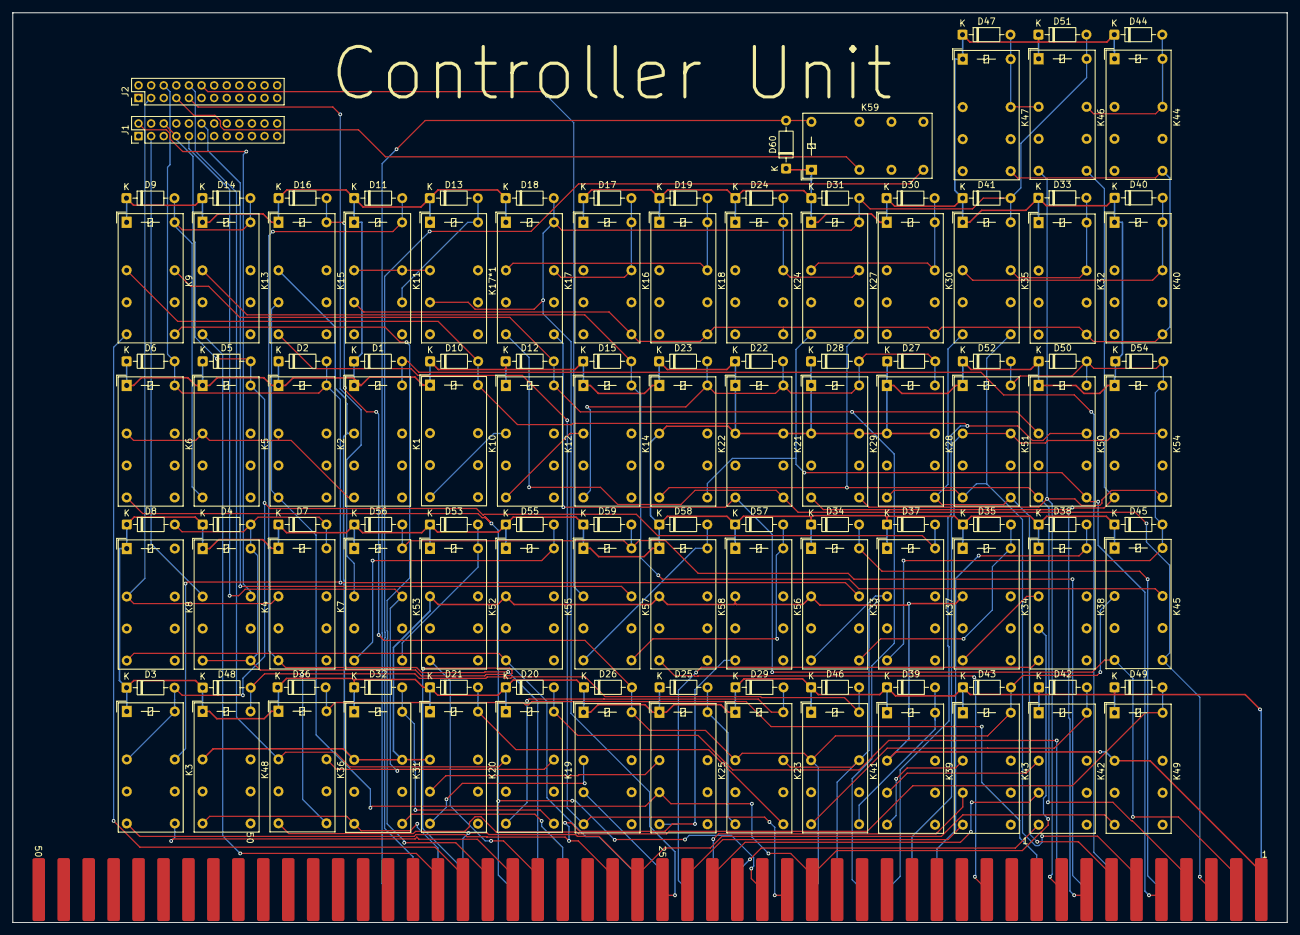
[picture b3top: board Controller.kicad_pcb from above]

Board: 2 copper layers, 202.3 x 144.4 mm, 123 parts (0 on the bottom side), 92 nets.

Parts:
D1, D2, D3, D4, D5, D6, D7, D8, D9, D10, D11, D12, D13, D14, D15, D16, D17, D18, D19, D20, D21, D22, D23, D24, D25, D26, D27, D28, D29, D30, D31, D32, D33, D34, D35, D36, D37, D38, D39, D40, D41, D42, D43, D44, D45, D46, D47, D48, D49, D50, D51, D52, D53, D54, D55, D56, D57, D58, D59, D60: 1N914; D_DO-35_SOD27_P7.62mm_Horizontal
J1, J2: Conn_02x12_Counter_Clockwise; PinHeader_2x12_P2.00mm_Vertical
K1, K2, K3, K4, K5, K6, K7, K8, K9, K10, K11, K12, K13, K14, K15, K16, K17, K17*1, K18, K19, K20, K21, K22, K23, K24, K25, K26, K27, K28, K29, K30, K31, K32, K33, K34, K35, K36, K37, K38, K39, K40, K41, K42, K43, K44, K45, K46, K47, K48, K49, K50, K51, K52, K53, K54, K55, K56, K57, K58, K59: HK19F-DCxxV-SHC; Relay_DPDT_Finder_30.22
U1: Conn_RC_Male_100

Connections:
5 V: K11.11, K11.21, K17*1.11
+5V: K1.11, K15.11, K20.11, K31.11, K31.21, K33.11, K34.11, K39.11, K48.11, K49.11, K52.11, K55.11, K56.11, K58.11, U1.1 (5_Volt)
ALD: K2.14, K15.12, K25.12, K38.12, U1.19 (ALD)
ALU: D1.2 (A), K1.A2, U1.57 (IALU)
ASL: K42.12, U1.23 (ASL)
BLD: K25.14, K38.14, U1.74 (BLD)
BSL: K42.14, U1.72 (BSL)
CLD: K26.12, U1.75 (CLD)
CSL: K43.12, U1.73 (CSL)
D0: K17.24, K21.14, K45.14, U1.2 (D0)
D1: K17.14, K21.24, K45.24, U1.3 (D1)
D2: K22.14, K27.24, K50.14, U1.4 (D2)
D3: K22.24, K27.14, K50.24, U1.5 (D3)
D4: K28.14, K35.24, K51.14, U1.6 (D4)
D5: K28.24, K35.14, K51.24, U1.7 (D5)
D6: K29.14, K46.24, K54.14, U1.8 (D6)
D7: K29.24, K46.14, K54.24, U1.9 (D7)
DLD: K15.14, K26.14, U1.20 (DLD)
DSL: K43.14, U1.24 (DSL)
F1: K9.24, U1.32 (F1)
F2: K9.14, U1.33 (F2)
F3: K13.14, U1.34 (F3)
GND: D1.1 (K), D2.1 (K), D3.1 (K), D4.1 (K), D5.1 (K), D6.1 (K), D7.1 (K), D8.1 (K), D9.1 (K), D10.1 (K), D11.1 (K), D12.1 (K), D13.1 (K), D14.1 (K), D15.1 (K), D16.1 (K), D17.1 (K), D18.1 (K), D19.1 (K), D20.1 (K), D21.1 (K), D22.1 (K), D23.1 (K), D24.1 (K), D25.1 (K), D26.1 (K), D27.1 (K), D28.1 (K), D29.1 (K), D30.1 (K), D31.1 (K), D32.1 (K), D33.1 (K), D34.1 (K), D35.1 (K), D36.1 (K), D37.1 (K), D38.1 (K), D39.1 (K), D40.1 (K), D41.1 (K), D42.1 (K), D43.1 (K), D44.1 (K), D45.1 (K), D46.1 (K), D47.1 (K), D48.1 (K), D49.1 (K), D50.1 (K), D51.1 (K), D52.1 (K), D53.1 (K), D54.1 (K), D55.1 (K), D56.1 (K), D57.1 (K), D58.1 (K), D59.1 (K), D60.1 (K), K1.A1, K2.A1, K3.A1, K4.A1, K5.A1, K6.A1, K7.A1, K8.A1, K9.A1, K10.A1, K11.A1, K12.A1, K13.A1, K14.A1, K15.A1, K16.A1, K17.A1, K17*1.A1, K18.A1, K19.A1, K20.A1, K21.11, K21.21, K21.A1, K22.11, K22.A1, K23.A1, K24.A1, K25.A1, K26.A1, K27.A1, K28.11, K28.21, K28.A1, K29.11, K29.21, K29.A1, K30.A1, K31.A1, K32.A1, K33.A1, K34.A1, K35.A1, K36.A1, K37.A1, K38.A1, K39.A1, K40.A1, K41.A1, K42.A1, K43.A1, K44.A1, K45.A1, K46.A1, K47.A1, K48.A1, K49.A1, K50.A1, K51.A1, K52.A1, K53.A1, K54.A1, K55.A1, K56.A1, K57.A1, K58.A1, K59.A1, U1.51 (GND)
HALT: K59.14, U1.85 (NC)
ILOD: D20.2 (A), K19.A2, U1.59 (ILOD)
IM2BSET: D45.2 (A), D50.2 (A), D52.2 (A), D54.2 (A), K37.14, K45.A2, K50.A2, K51.A2, K54.A2
IMISC: D60.2 (A), K59.A2, U1.86 (NC)
INC: D56.2 (A), D59.2 (A), K53.A2, K57.A2, U1.58 (IINC)
ISTR: D36.2 (A), K36.A2, U1.60 (ISTR)
LdCCReg: K6.14, U1.21 (ADLD), U1.81 (CCRegLD)
LdINC: K8.14, K55.14, U1.76 (INCLD)
LdINST: D11.2 (A), K7.14, K11.A2, U1.80 (INSTLD)
LdPC: K3.24, U1.31 (PCLD)
LdXY: K58.14, U1.12 (XYLD)
MEMLD: D4.2 (A), D7.2 (A), D8.2 (A), K4.14, K4.24, K4.A2, K7.A2, K49.14, U1.26 (PCSL), U1.83 (MEMWRITE)
MEMRD: K31.24, U1.79 (MEMREAD)
MEMSL: K31.14, K48.14, U1.84 (MEMSL)
unnamed: D13.2 (A), K11.22, K17*1.A2
unnamed: D9.2 (A), D14.2 (A), K5.14, K9.A2, K13.A2
unnamed: D17.2 (A), K16.21, K16.A2, K17.21
unnamed: D19.2 (A), K17.11, K18.21, K18.A2
unnamed: D21.2 (A), K20.A2, K23.24
unnamed: D22.2 (A), D23.2 (A), D27.2 (A), D28.2 (A), K14.14, K21.A2, K22.A2, K28.A2, K29.A2
unnamed: D24.2 (A), K24.21, K24.A2, K27.21
unnamed: D25.2 (A), K23.14, K25.A2
unnamed: D29.2 (A), K19.14, K23.A2
unnamed: D30.2 (A), K27.11, K30.21, K30.A2
unnamed: D32.2 (A), K19.24, K31.A2
unnamed: D33.2 (A), K32.21, K32.A2, K35.21
unnamed: D35.2 (A), K33.24, K34.A2
unnamed: D39.2 (A), K39.A2, K41.24
unnamed: D40.2 (A), K35.11, K40.21, K40.A2
unnamed: D42.2 (A), K41.14, K42.A2
unnamed: D44.2 (A), K44.21, K44.A2, K46.21
unnamed: D46.2 (A), D48.2 (A), K36.24, K41.A2, K48.A2
unnamed: D47.2 (A), K46.11, K47.21, K47.A2
unnamed: D49.2 (A), K36.14, K49.A2
unnamed: D53.2 (A), K52.A2, K53.24
unnamed: D55.2 (A), K53.14, K55.A2
unnamed: D57.2 (A), K56.A2, K57.24
unnamed: D58.2 (A), K57.14, K58.A2
unnamed: K1.14, K2.11, K5.11, K6.11
unnamed: K10.14, K12.11
unnamed: K11.12, K16.24, K18.24, K24.24, K30.24, K32.24, K40.24, K44.24, K47.24
unnamed: K12.14, K14.11
unnamed: K20.12, K25.11
unnamed: K20.14, K26.11
unnamed: K33.14, K37.11
unnamed: K34.14, K38.11
unnamed: K39.12, K42.11
unnamed: K39.14, K43.11
S1: J1.2, K4.21
S2: J1.3, K4.11
S2': J2.3, K7.11, K8.11
S5: D3.2 (A), D5.2 (A), D37.2 (A), J1.6, J1.7, K3.11, K3.A2, K5.A2, K37.A2
S5': D2.2 (A), D6.2 (A), J2.6, K2.A2, K3.21, K6.A2, K33.21
S6': J2.7, K59.11
S8: J1.9, K19.21, K36.21, K53.21
S8': J2.9, K53.11
S9': J2.10, K19.11, K36.11
S11: J1.12, K57.21
S11': J2.12, K57.11
SET: D34.2 (A), K33.A2, U1.55 (ISET)
SelINC: K3.14, K56.14, U1.27 (IncSL)
SelXY: K52.14, U1.30 (XYSL)
Select: D18.2 (A), D31.2 (A), D41.2 (A), D51.2 (A), K17.A2, K17*1.12, K27.A2, K35.A2, K46.A2, U1.25 (InstSL)
Val1: K51.11, K51.21, K54.11, K54.21, U1.65 (I4)
Val2: D10.2 (A), K9.11, K10.A2, K50.21, U1.66 (I3)
Val3: D12.2 (A), K9.21, K12.A2, K50.11, U1.67 (I2)
Val4: D15.2 (A), K13.11, K14.A2, K23.21, K41.21, K45.21, U1.68 (I1)
Val5: D16.2 (A), D26.2 (A), D43.2 (A), K15.A2, K23.11, K26.A2, K41.11, K43.A2, K45.11, U1.69 (I0)
destRegSET: D38.2 (A), K38.A2, U1.64 (I5)
